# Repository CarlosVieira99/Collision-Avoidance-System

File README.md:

# Colllision-Avoidance-System
Project developed during the first year of the Masters Degree. The goal was to build a flexible collision avoidance solution to use in big sized UAVs. The project includes: STM32 Microcontroller, LiDAR Sensor, CAN/RS232/RS485 Communication. Powered by 12V.

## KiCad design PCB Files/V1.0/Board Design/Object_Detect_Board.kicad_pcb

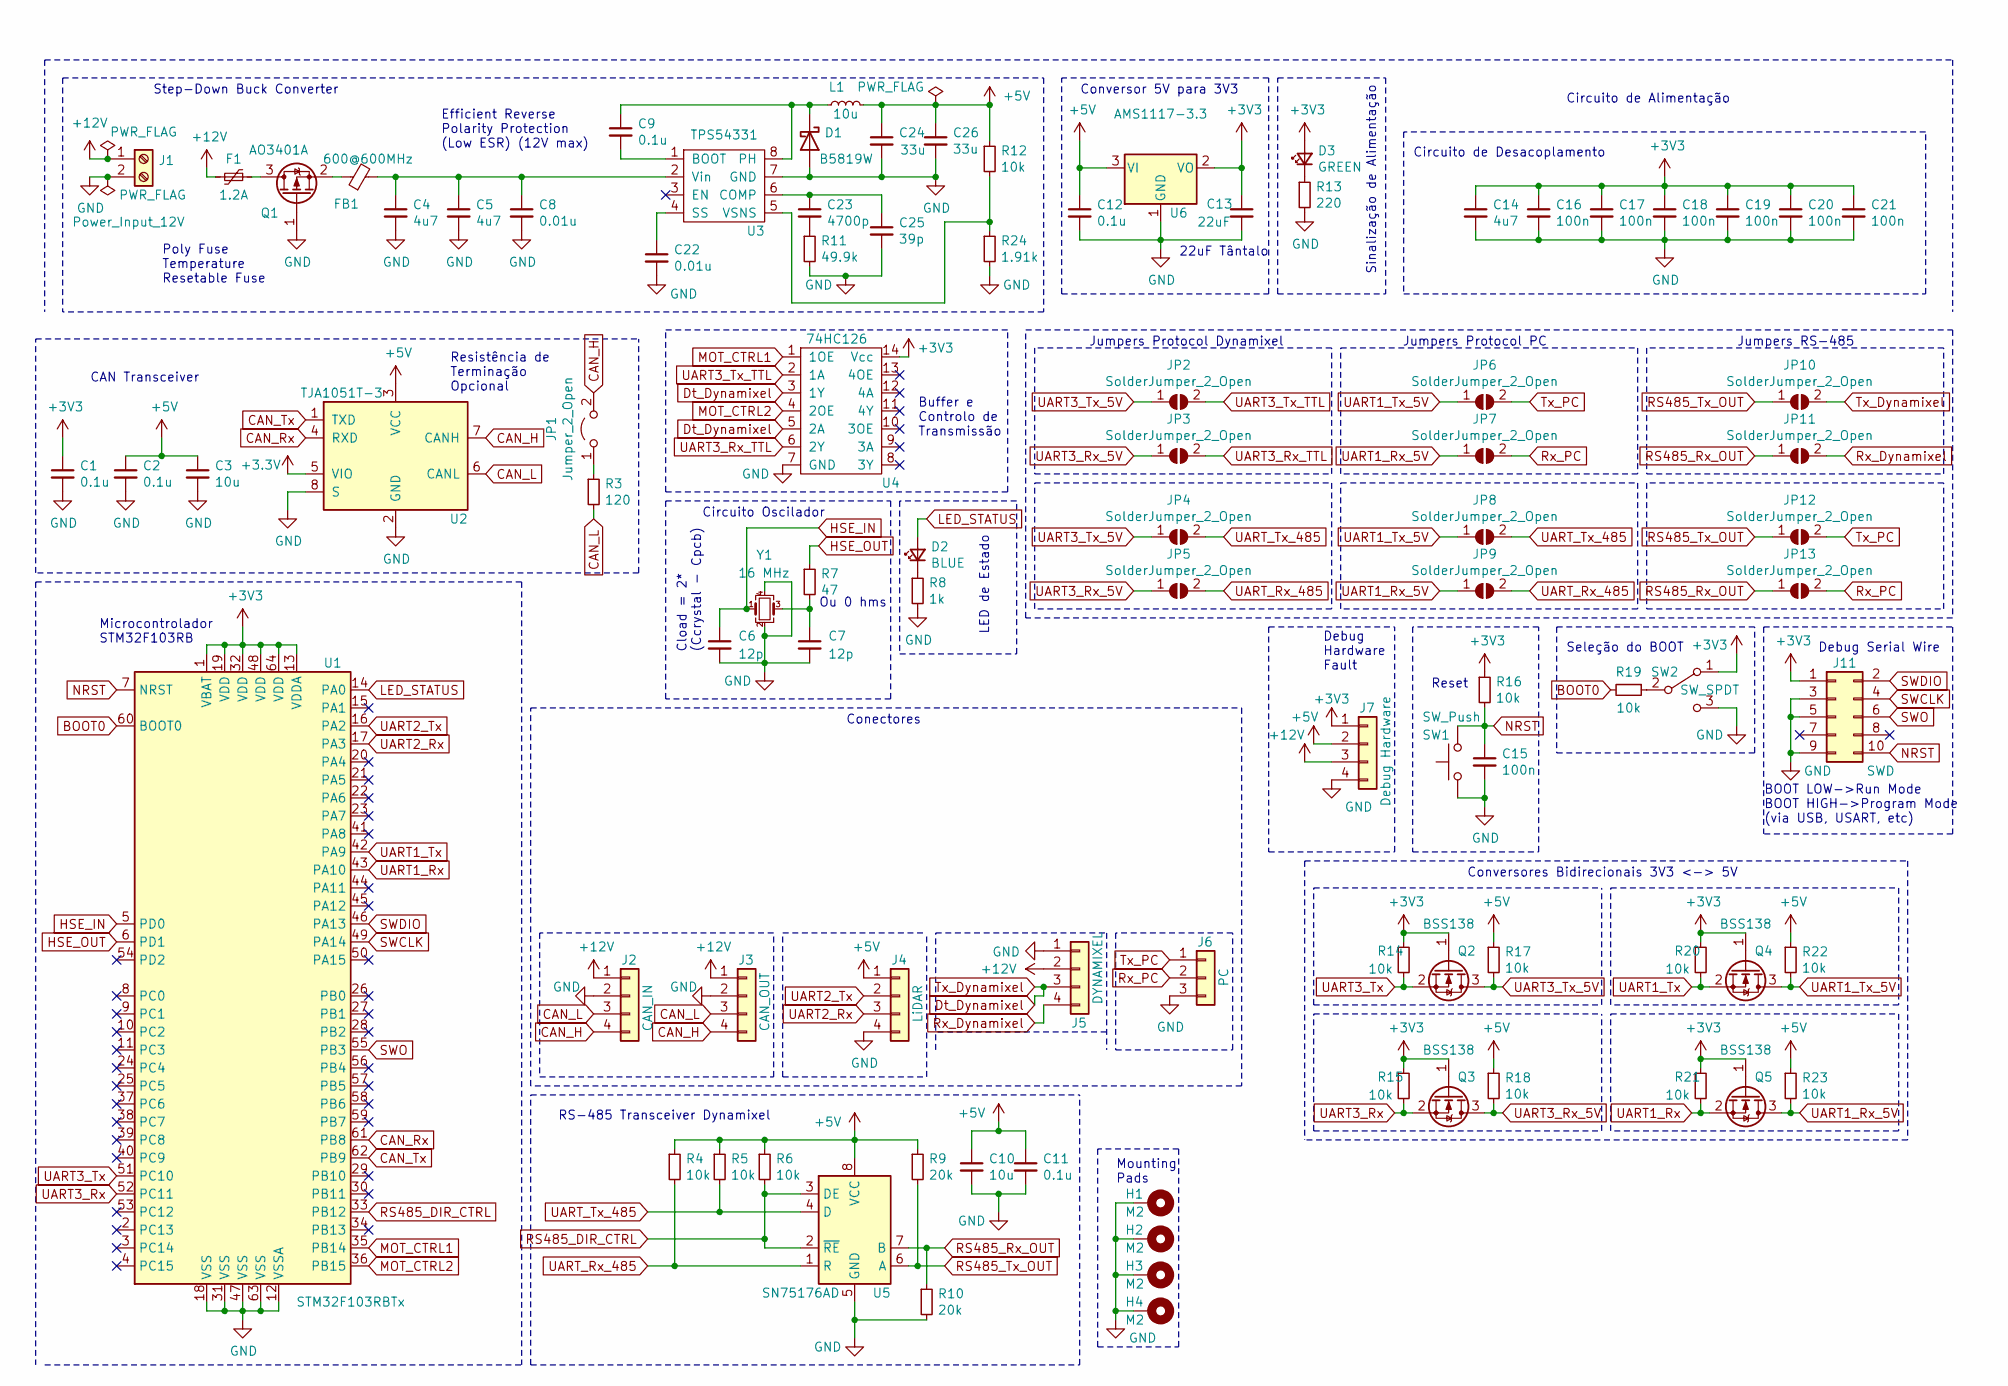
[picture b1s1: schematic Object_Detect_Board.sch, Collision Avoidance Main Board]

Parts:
C1, C2, C11: 0.1u; C_0402_1005Metric; LCSC Part # C1525
C3, C10: 10u; C_0402_1005Metric; LCSC Part # C15525
C4, C5: 4u7; C_1206_3216Metric; LCSC Part # C29823
C6, C7: 12p; C_0402_1005Metric; LCSC Part # C1547
C8, C22: 0.01u; C_1206_3216Metric; LCSC Part # C1846
C9, C12: 0.1u; C_1206_3216Metric; LCSC Part # C24497
C13: 22uF; C_0805_2012Metric; LCSC Part # C45783
C14: 4u7; C_0603_1608Metric; LCSC Part # C19666
C15, C16, C17, C18, C19, C20, C21: 100n; C_0402_1005Metric; LCSC Part # C1525
C23: 4700p; C_0805_2012Metric; LCSC Part # C1744
C24, C26: 33u; CP_EIA-3528-21_Kemet-B; LCSC Part # C139576
C25: 39p; C_0603_1608Metric; LCSC Part # C53278
D1: B5819W; D_SOD-123; LCSC Part # C8598
D2: BLUE; LED_0603_1608Metric; LCSC Part # C72041
D3: GREEN; LED_0603_1608Metric; LCSC Part # C72043
F1: 1.2A; Fuse_1206_3216Metric; LCSC Part # C70082
FB1: 600@600MHz; L_0805_2012Metric; LCSC Part # C1017
H1, H2, H3, H4: M2; MountingHole_2.2mm_M2_Pad_Via
J1: Power_Input_12V; Molex_Micro-Fit_3.0_43045-0200_2x01_P3.00mm_Horizontal; LCSC Part C29823
J2: CAN_IN; Molex_Micro-Fit_3.0_43045-0400_2x02_P3.00mm_Horizontal
J3: CAN_OUT; Molex_Micro-Fit_3.0_43045-0400_2x02_P3.00mm_Horizontal
J4: LiDAR; Molex_PicoBlade_53047-0410_1x04_P1.25mm_Vertical
J5: DYNAMIXEL; MOLEX_22-03-5045
J6: PC; MOLEX_22-03-5035
J7: Debug Hardware; PinHeader_1x04_P1.27mm_Vertical
J11: SWD; PinHeader_2x05_P1.27mm_Vertical_SMD
JP1: Jumper_2_Open; PinHeader_1x02_P2.54mm_Vertical
JP2, JP3, JP4, JP5, JP6, JP7, JP8, JP9, JP10, JP11, JP12, JP13: SolderJumper_2_Open; SolderJumper-2_P1.3mm_Open_RoundedPad1.0x1.5mm
L1: 10u; L_Sunlord_MWSA0518_5.4x5.2mm; LCSC Part # C408412
Q1: AO3401A; SOT-23; LCSC Part # C15127
Q2, Q3, Q4, Q5: BSS138; SOT-23; LCSC Part # C112239
R3: 120; R_0402_1005Metric; LCSC Part # C25079
R4, R5, R6, R14, R15, R16, R17, R18, R19, R20, R21, R22, R23: 10k; R_0402_1005Metric; LCSC Part # C25744
R7: 47; R_0402_1005Metric; LCSC Part # C25118
R8: 1k; R_0603_1608Metric; LCSC Part # C21190
R9, R10: 20k; R_0402_1005Metric; LCSC Part # C25765
R11: 49.9k; R_0603_1608Metric; LCSC Part # C23184
R12: 10k; R_0603_1608Metric; LCSC Part # C25804
R13: 220; R_0603_1608Metric; LCSC Part # C22962
R24: 1.91k; R_0603_1608Metric; LCSC Part # C22853
SW1: SW_Push; SW_SPST_B3U-1000P
SW2: SW_SPDT; SW_SPDT_PCM12
U1: STM32F103RBTx; LQFP-64_10x10mm_P0.5mm; LCSC Part # C8735
U2: TJA1051T-3; SOIC-8_3.9x4.9mm_P1.27mm; LCSC Part # C38695
U3: TPS54331; SOIC-8_3.9x4.9mm_P1.27mm; LCSC Part # C9865
U4: 74HC126; SOIC-14_3.9x8.7mm_P1.27mm; LCSC Part # C5600
U5: SN75176AD; SOIC-8_3.9x4.9mm_P1.27mm; LCSC Part # C7063
U6: AMS1117-3.3; SOT-223; LCSC Part # C6186
Y1: 16 MHz; Crystal_SMD_3225-4Pin_3.2x2.5mm; LCSC Part # C13738

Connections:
+5V: C2.1, C3.1, C10.1, C11.1, C12.1, C24.1, C26.1, J4.1, J7.2, L1.2, R4.1, R5.1, R6.1, R9.1, R12.1, R17.1, R18.1, R22.1, R23.1, U2.3 (VCC), U5.8 (VCC), U6.3 (VI); also elsewhere on the board
+12V: F1.2, J1.1, J2.1, J3.1, J5.2, J7.3; also elsewhere on the board
BOOT0: R19.2, U1.60 (BOOT0)
CAN_H: J2.4, J3.4, JP1.2 (B), U2.7 (CANH)
CAN_L: J2.3, J3.3, R3.2, U2.6 (CANL)
CAN_Rx: U1.61 (PB8), U2.4 (RXD)
CAN_Tx: U1.62 (PB9), U2.1 (TXD)
Dt_Dynamixel: J5.3, JP10.2 (B), U4.3 (1Y), U4.5 (2A)
GND: C1.2, C2.2, C3.2, C4.2, C5.2, C6.2, C7.2, C8.2, C10.2, C11.2, C12.2, C13.2, C14.2, C15.2, C16.2, C17.2, C18.2, C19.2, C20.2, C21.2, C22.2, C24.2, C25.2, C26.2, D1.2 (A), H1.1, H2.1, H3.1, H4.1, J1.2, J2.2, J3.2, J4.4, J5.1, J6.3, J7.4, J11.3, J11.5, J11.9, Q1.1 (G), R8.2, R10.2, R11.2, R13.2, R24.2, SW1.1, SW2.3 (C), U1.12 (VSSA), U1.18 (VSS), U1.31 (VSS), U1.47 (VSS), U1.63 (VSS), U2.2 (GND), U2.8 (S), U3.7 (GND), U4.7 (GND), U5.5 (GND), U6.1 (GND), Y1.2, Y1.4; also elsewhere on the board
HSE_IN: C6.1, U1.5 (PD0), Y1.1
HSE_OUT: R7.1, U1.6 (PD1)
LED_STATUS: D2.2 (A), U1.14 (PA0)
MOT_CTRL1: U1.35 (PB14), U4.1 (1OE)
MOT_CTRL2: U1.36 (PB15), U4.4 (2OE)
NRST: C15.1, J11.10, R16.2, SW1.2, U1.7 (NRST); also elsewhere on the board
unnamed: C4.1, C5.1, C8.1, FB1.2, U3.2 (Vin)
unnamed: C7.1, R7.2, Y1.3
unnamed: C9.1, D1.1 (K), L1.1, U3.8 (PH)
unnamed: C9.2, U3.1 (BOOT)
unnamed: C22.1, U3.4 (SS)
unnamed: C23.1, C25.1, U3.6 (COMP)
unnamed: C23.2, R11.1
unnamed: D2.1 (K), R8.1
unnamed: D3.1 (K), R13.1
unnamed: F1.1, Q1.3 (D)
unnamed: FB1.1, Q1.2 (S)
unnamed: JP1.1 (A), R3.1
unnamed: R12.2, R24.1, U3.5 (VSNS)
unnamed 30: R19.1, SW2.2 (B); also elsewhere on the board
RS485_DIR_CTRL: R6.2, U1.33 (PB12), U5.2 (~RE), U5.3 (DE)
RS485_Rx_OUT: JP11.1 (A), JP13.1 (A), R10.1, U5.7 (B)
RS485_Tx_OUT: JP10.1 (A), JP12.1 (A), R9.2, U5.6 (A)
Rx_Dynamixel: J5.4, JP11.2 (B)
Rx_PC: J6.2, JP7.2 (B), JP13.2 (B)
SWCLK: J11.4, U1.49 (PA14)
SWDIO: J11.2, U1.46 (PA13)
SWO: J11.6, U1.55 (PB3)
Tx_PC: J6.1, JP6.2 (B), JP12.2 (B)
UART1_Rx: Q5.2 (S), R21.2, U1.43 (PA10)
UART1_Rx_5V: JP7.1 (A), JP9.1 (A), Q5.3 (D), R23.2
UART1_Tx: Q4.2 (S), R20.2, U1.42 (PA9)
UART1_Tx_5V: JP6.1 (A), JP8.1 (A), Q4.3 (D), R22.2
UART2_Rx: J4.3, U1.17 (PA3)
UART2_Tx: J4.2, U1.16 (PA2)
UART3_Rx: Q3.2 (S), R15.2, U1.52 (PC11)
UART3_Rx_5V: JP3.1 (A), JP5.1 (A), Q3.3 (D), R18.2
UART3_Rx_TTL: JP3.2 (B), U4.6 (2Y)
UART3_Tx: Q2.2 (S), R14.2, U1.51 (PC10)
UART3_Tx_5V: JP2.1 (A), JP4.1 (A), Q2.3 (D), R17.2
UART3_Tx_TTL: JP2.2 (B), U4.2 (1A)
UART_Rx_485: JP5.2 (B), JP9.2 (B), R4.2, U5.1 (R)
UART_Tx_485: JP4.2 (B), JP8.2 (B), R5.2, U5.4 (D)

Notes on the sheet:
BOOT LOW->Run Mode BOOT HIGH->Program Mode (via USB, USART, etc)
Cload = 2* (Ccrystal - Cpcb)
Ou 0 hms
22uF Tântalo
Circuito Oscilador
Debug Serial Wire
Seleção do BOOT
Circuito de Alimentação
Conversor 5V para 3V3
Sinalização de Alimentação
Microcontrolador STM32F103RB
Circuito de Desacoplamento
Buffer e Controlo de Transmissão
Debug Hardware Fault
Poly Fuse Temperature Resetable Fuse
Efficient Reverse Polarity Protection (Low ESR) (12V max)
CAN Transceiver
Resistência de Terminação Opcional
Conversores Bidirecionais 3V3 <-> 5V
RS-485 Transceiver Dynamixel
LED de Estado
Mounting Pads
Jumpers Protocol Dynamixel
Jumpers Protocol PC
Jumpers RS-485
Reset
Step-Down Buck Converter
Conectores

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
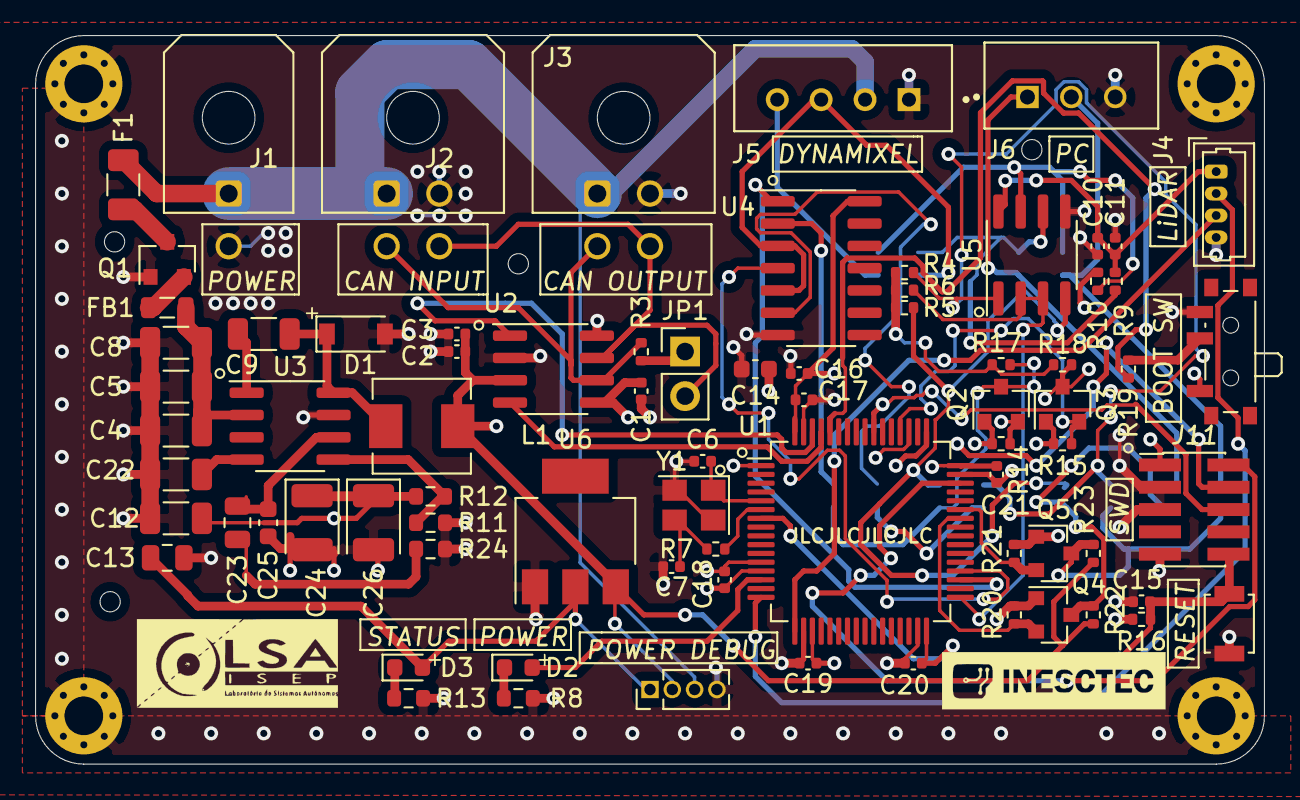
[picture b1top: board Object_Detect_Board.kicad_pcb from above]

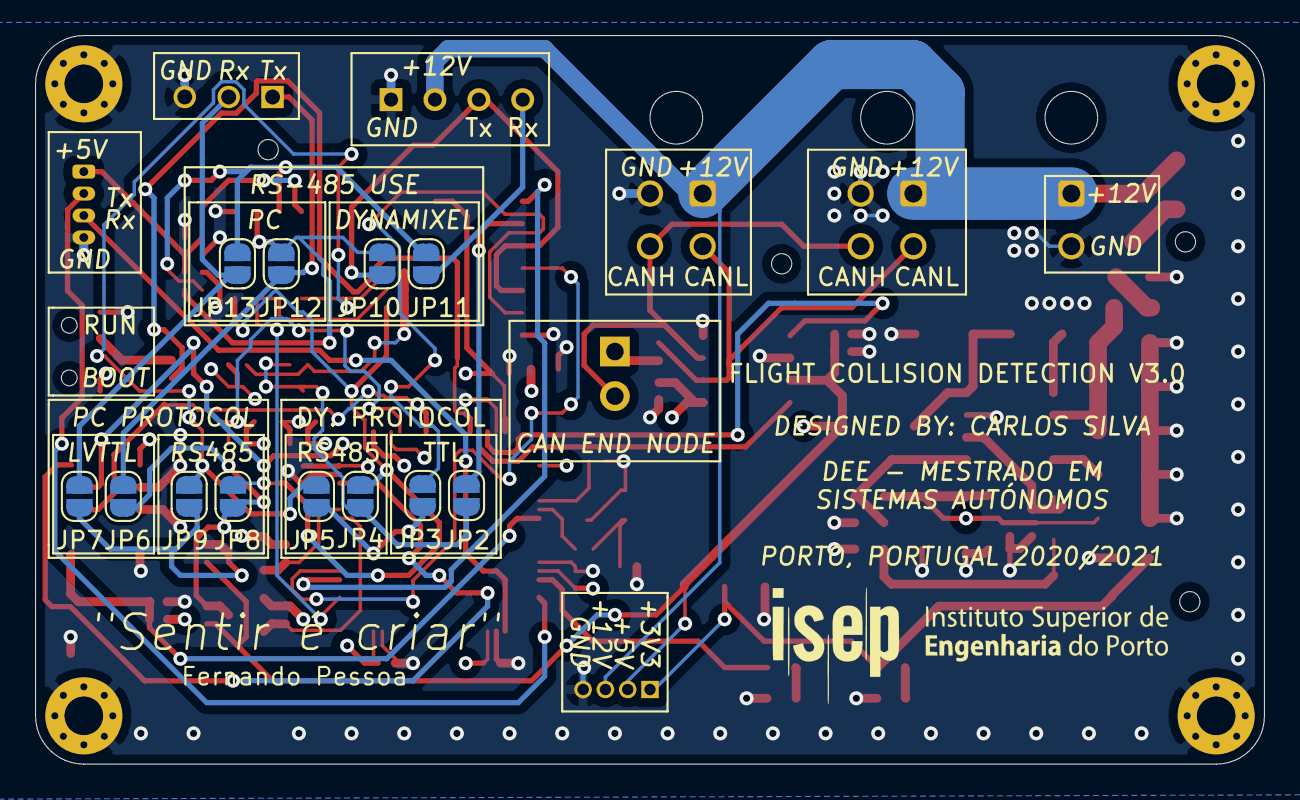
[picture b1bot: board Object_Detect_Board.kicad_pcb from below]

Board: 4 copper layers, 70.0 x 41.5 mm, 93 parts (12 on the bottom side), 53 nets.

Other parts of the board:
BOOT SW: SW_SPDT; SW_SPDT_PCM12
POWER DEBUG: Debug Hardware; PinHeader_1x04_P1.27mm_Vertical
RESET: SW_Push; SW_SPST_B3U-1000P

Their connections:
+5V: POWER DEBUG.2; also elsewhere on the board
+12V: POWER DEBUG.3; also elsewhere on the board
GND: BOOT SW.3, POWER DEBUG.4, RESET.1; also elsewhere on the board
NRST: RESET.2; also elsewhere on the board
unnamed 30: BOOT SW.2; also elsewhere on the board

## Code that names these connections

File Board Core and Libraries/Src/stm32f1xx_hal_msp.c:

/* USER CODE BEGIN Header */
/**
  ******************************************************************************
  * @file         stm32f1xx_hal_msp.c
  * @brief        This file provides code for the MSP Initialization
  *               and de-Initialization codes.
  ******************************************************************************
  * @attention
  *
  * <h2><center>&copy; Copyright (c) 2021 STMicroelectronics.
  * All rights reserved.</center></h2>
  *
  * This software component is licensed by ST under BSD 3-Clause license,
  * the "License"; You may not use this file except in compliance with the
  * License. You may obtain a copy of the License at:
  *                        opensource.org/licenses/BSD-3-Clause
  *
  ******************************************************************************
  */
/* USER CODE END Header */

/* Includes ------------------------------------------------------------------*/
#include "main.h"
/* USER CODE BEGIN Includes */

/* USER CODE END Includes */

/* Private typedef -----------------------------------------------------------*/
/* USER CODE BEGIN TD */

/* USER CODE END TD */

/* Private define ------------------------------------------------------------*/
/* USER CODE BEGIN Define */

/* USER CODE END Define */

/* Private macro -------------------------------------------------------------*/
/* USER CODE BEGIN Macro */

/* USER CODE END Macro */

/* Private variables ---------------------------------------------------------*/
/* USER CODE BEGIN PV */

/* USER CODE END PV */

/* Private function prototypes -----------------------------------------------*/
/* USER CODE BEGIN PFP */

/* USER CODE END PFP */

/* External functions --------------------------------------------------------*/
/* USER CODE BEGIN ExternalFunctions */

/* USER CODE END ExternalFunctions */

/* USER CODE BEGIN 0 */

/* USER CODE END 0 */
/**
  * Initializes the Global MSP.
  */
void HAL_MspInit(void)
{
  /* USER CODE BEGIN MspInit 0 */

  /* USER CODE END MspInit 0 */

  __HAL_RCC_AFIO_CLK_ENABLE();
  __HAL_RCC_PWR_CLK_ENABLE();

  /* System interrupt init*/
  /* PendSV_IRQn interrupt configuration */
  HAL_NVIC_SetPriority(PendSV_IRQn, 15, 0);

  /** NOJTAG: JTAG-DP Disabled and SW-DP Enabled
  */
  __HAL_AFIO_REMAP_SWJ_NOJTAG();

  /* USER CODE BEGIN MspInit 1 */

  /* USER CODE END MspInit 1 */
}

/**
* @brief UART MSP Initialization
* This function configures the hardware resources used in this example
* @param huart: UART handle pointer
* @retval None
*/
void HAL_UART_MspInit(UART_HandleTypeDef* huart)
{
  GPIO_InitTypeDef GPIO_InitStruct = {0};
  if(huart->Instance==USART1)
  {
  /* USER CODE BEGIN USART1_MspInit 0 */

  /* USER CODE END USART1_MspInit 0 */
    /* Peripheral clock enable */
    __HAL_RCC_USART1_CLK_ENABLE();

    __HAL_RCC_GPIOA_CLK_ENABLE();
    /**USART1 GPIO Configuration
    PA9     ------> USART1_TX
    PA10     ------> USART1_RX
    */
    GPIO_InitStruct.Pin = GPIO_PIN_9;
    GPIO_InitStruct.Mode = GPIO_MODE_AF_PP;
    GPIO_InitStruct.Speed = GPIO_SPEED_FREQ_HIGH;
    HAL_GPIO_Init(GPIOA, &GPIO_InitStruct);

    GPIO_InitStruct.Pin = GPIO_PIN_10;
    GPIO_InitStruct.Mode = GPIO_MODE_INPUT;
    GPIO_InitStruct.Pull = GPIO_NOPULL;
    HAL_GPIO_Init(GPIOA, &GPIO_InitStruct);

  /* USER CODE BEGIN USART1_MspInit 1 */

  /* USER CODE END USART1_MspInit 1 */
  }
  else if(huart->Instance==USART2)
  {
  /* USER CODE BEGIN USART2_MspInit 0 */

  /* USER CODE END USART2_MspInit 0 */
    /* Peripheral clock enable */
    __HAL_RCC_USART2_CLK_ENABLE();

    __HAL_RCC_GPIOA_CLK_ENABLE();
    /**USART2 GPIO Configuration
    PA2     ------> USART2_TX
    PA3     ------> USART2_RX
    */
    GPIO_InitStruct.Pin = GPIO_PIN_2;
    GPIO_InitStruct.Mode = GPIO_MODE_AF_PP;
    GPIO_InitStruct.Speed = GPIO_SPEED_FREQ_HIGH;
    HAL_GPIO_Init(GPIOA, &GPIO_InitStruct);

    GPIO_InitStruct.Pin = GPIO_PIN_3;
    GPIO_InitStruct.Mode = GPIO_MODE_INPUT;
    GPIO_InitStruct.Pull = GPIO_NOPULL;
    HAL_GPIO_Init(GPIOA, &GPIO_InitStruct);

  /* USER CODE BEGIN USART2_MspInit 1 */

  /* USER CODE END USART2_MspInit 1 */
  }
  else if(huart->Instance==USART3)
  {
  /* USER CODE BEGIN USART3_MspInit 0 */

  /* USER CODE END USART3_MspInit 0 */
    /* Peripheral clock enable */
    __HAL_RCC_USART3_CLK_ENABLE();

    __HAL_RCC_GPIOC_CLK_ENABLE();
    /**USART3 GPIO Configuration
    PC10     ------> USART3_TX
    PC11     ------> USART3_RX
    */
    GPIO_InitStruct.Pin = GPIO_PIN_10;
    GPIO_InitStruct.Mode = GPIO_MODE_AF_PP;
    GPIO_InitStruct.Speed = GPIO_SPEED_FREQ_HIGH;
    HAL_GPIO_Init(GPIOC, &GPIO_InitStruct);

    GPIO_InitStruct.Pin = GPIO_PIN_11;
    GPIO_InitStruct.Mode = GPIO_MODE_INPUT;
    GPIO_InitStruct.Pull = GPIO_NOPULL;
    HAL_GPIO_Init(GPIOC, &GPIO_InitStruct);

    __HAL_AFIO_REMAP_USART3_PARTIAL();

  /* USER CODE BEGIN USART3_MspInit 1 */

  /* USER CODE END USART3_MspInit 1 */
  }

}

/**
* @brief UART MSP De-Initialization
* This function freeze the hardware resources used in this example
* @param huart: UART handle pointer
* @retval None
*/
void HAL_UART_MspDeInit(UART_HandleTypeDef* huart)
{
  if(huart->Instance==USART1)
  {
  /* USER CODE BEGIN USART1_MspDeInit 0 */

  /* USER CODE END USART1_MspDeInit 0 */
    /* Peripheral clock disable */
    __HAL_RCC_USART1_CLK_DISABLE();

    /**USART1 GPIO Configuration
    PA9     ------> USART1_TX
    PA10     ------> USART1_RX
    */
    HAL_GPIO_DeInit(GPIOA, GPIO_PIN_9|GPIO_PIN_10);

  /* USER CODE BEGIN USART1_MspDeInit 1 */

  /* USER CODE END USART1_MspDeInit 1 */
  }
  else if(huart->Instance==USART2)
  {
  /* USER CODE BEGIN USART2_MspDeInit 0 */

  /* USER CODE END USART2_MspDeInit 0 */
    /* Peripheral clock disable */
    __HAL_RCC_USART2_CLK_DISABLE();

    /**USART2 GPIO Configuration
    PA2     ------> USART2_TX
    PA3     ------> USART2_RX
    */
    HAL_GPIO_DeInit(GPIOA, GPIO_PIN_2|GPIO_PIN_3);

  /* USER CODE BEGIN USART2_MspDeInit 1 */

  /* USER CODE END USART2_MspDeInit 1 */
  }
  else if(huart->Instance==USART3)
  {
  /* USER CODE BEGIN USART3_MspDeInit 0 */

  /* USER CODE END USART3_MspDeInit 0 */
    /* Peripheral clock disable */
    __HAL_RCC_USART3_CLK_DISABLE();

    /**USART3 GPIO Configuration
    PC10     ------> USART3_TX
    PC11     ------> USART3_RX
    */
    HAL_GPIO_DeInit(GPIOC, GPIO_PIN_10|GPIO_PIN_11);

  /* USER CODE BEGIN USART3_MspDeInit 1 */

  /* USER CODE END USART3_MspDeInit 1 */
  }

}

/* USER CODE BEGIN 1 */

/* USER CODE END 1 */

/************************ (C) COPYRIGHT STMicroelectronics *****END OF FILE****/
